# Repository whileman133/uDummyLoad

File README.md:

# 20W/50Ω μDummy RF Load with Wattmeter

This is the home of the design files and firmware for the μDummy RF Load project. See the description of the unit and the resources in this repo below.

## Description

This micro-size 50Ω RF dummy load with built-in wattmeter is well-suited for testing portable rigs. 
The glass LCD provides time-average power readings between 0.15 and 20W with 0.1W precision. 
Batteries are not required, as the unit draws power from the RF source, consuming a maximum of 3.0mA at the full rated input power. 
The board itself serves as a heatsink provided the operator limits the duration of the RF input. 
Improve the accuracy by loading a calibration table of up to 60 rows into EEPROM using an Arduino microcontroller.

## Organization of this Repo

- `2_Documentation/`: datasheet and documentation for the μDummy load unit
- `3_Mechanical/`: mechanical design files (primarily thermal analysis)
- `3_Electrical/`: KiCAD design files and LTspice simulation files
- `4_Software/`: firmware files
  - `uDummyLoad_PIC18F24Q10.X/`: firmware for the PIC microcontroller
  - `uDummyLoad_TranslatorArduino/`: Arduino sketch for uploading calibration table to the unit with an Arduino microcontroller

 ## License

Apache License, Version 2.0. See `LICENSE`.

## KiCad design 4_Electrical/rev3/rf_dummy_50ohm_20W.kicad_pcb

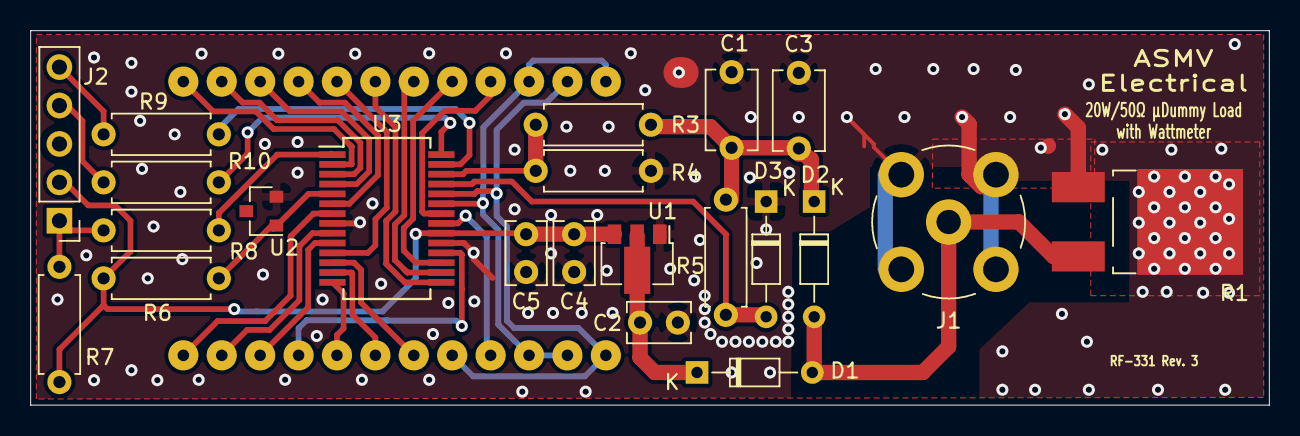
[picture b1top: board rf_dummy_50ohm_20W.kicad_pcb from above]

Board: 2 copper layers, 81.9 x 24.8 mm, 23 parts (1 on the bottom side), 33 nets.

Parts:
C1, C3: 5.6n; C_Disc_D5.1mm_W3.2mm_P5.00mm
C2: 1u 100V; C_Rect_L4.0mm_W2.5mm_P2.50mm
C4: 1u; C_Rect_L4.0mm_W2.5mm_P2.50mm
C5: 10n; C_Rect_L4.0mm_W2.5mm_P2.50mm
D1, D2, D3: BAT46; D_DO-34_SOD68_P7.62mm_Horizontal
J1: 50-Ohm BNC Male; BNC_TEConnectivity_1478204_Vertical
J2: Conn_01x05_Male; PinHeader_1x05_P2.54mm_Vertical
R1: 50 1% 45W; TO-252-2_TabPin1
R3: 100k 0.1%; R_Axial_DIN0207_L6.3mm_D2.5mm_P7.62mm_Horizontal
R4: 10k 0.1%; R_Axial_DIN0207_L6.3mm_D2.5mm_P7.62mm_Horizontal
R5, R7: 100k; R_Axial_DIN0207_L6.3mm_D2.5mm_P7.62mm_Horizontal
R6: 2.4k; R_Axial_DIN0207_L6.3mm_D2.5mm_P7.62mm_Horizontal
R8, R9, R10: 75; R_Axial_DIN0207_L6.3mm_D2.5mm_P7.62mm_Horizontal
U1: ZXTR2005Z; SOT-89-3
U2: LM4040AIM3-4.1; SOT-23
U3: PIC18F24Q10-xSP; SSOP-28_5.3x10.2mm_P0.65mm
U4: LCD-S301C31TF

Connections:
/ICSPCLK: J2.5, R9.1
/ICSPDAT: J2.4, R10.1
/LCD1_ADEG: U3.23, U4.2, U4.3, U4.22, U4.24
/LCD1_B: U3.22, U4.21
/LCD1_C: U3.21, U4.4
/LCD2_A: U3.15, U4.18
/LCD2_B: U3.11, U4.17
/LCD2_C: U3.14, U4.8
/LCD2_D: U3.13, U4.7
/LCD2_E: U3.12, U4.6
/LCD2_F: U3.16, U4.19
/LCD2_G: U3.17, U4.20
/LCD3_A: U3.3, U4.14
/LCD3_B: U3.2, U4.13
/LCD3_C: U3.7, U4.12
/LCD3_D: U3.9, U4.11
/LCD3_E: U3.10, U4.10
/LCD3_F: U3.4, U4.15
/LCD3_G: U3.6, U4.16
/LCD_COM: U3.24, U4.1, U4.5, U4.23
/LCD_DP2: U3.18, U4.9
/Vdiode: D3.2, R5.2, U3.25
/Vdivider: R3.1, R4.1, U3.26
/Vref+: R6.1, U2.1, U3.5
/~MCLR: J2.1, R7.2, R8.2
GND: C1.2, C2.2, C3.2, C4.2, C5.2, D3.1, J1.2, J2.3, R1.1, R4.2, U1.1, U2.2, U3.8, U3.19
unnamed: C1.1, C3.1, D2.1, R3.2, R5.1
unnamed: C2.1, D1.1, U1.2
unnamed: D1.2, D2.2, J1.1, R1.2
unnamed: R8.1, U3.1
unnamed: R9.2, U3.27
unnamed: R10.2, U3.28
VDD: C4.1, C5.1, J2.2, R6.2, R7.1, U1.3, U3.20

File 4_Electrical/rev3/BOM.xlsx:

Qty | Reference(s) | Value | Description | Man | Vendor | VendorPN | Quantity | Unit Price (1 assy) | Ext. Price (1 assy)
2 | C1, C3 | 5.6n | CAP CER 5600PF 100V C0G RADIAL |  | DigiKey | 445-181255-ND | 2 | 0.41 | 0.82
1 | C2, C4 | 1u 100V | CAP CER 1UF 100V X7R RADIAL | TDK Corporation | DigiKey | 445-173162-1-ND | 2 | 0.73 | 1.46
1 | C5 | 10n | CAP CER 10000PF 50V X7R RADIAL | TDK Corporation | DigiKey | 445-173264-1-ND | 1 | 0.28000000000000003 | 0.28000000000000003
3 | D1, D2, D3 | BAT46 | DIODE SCHOTTKY 100V 150MA DO35 | Vishay | DigiKey | BAT46CT-ND | 3 | 0.46 | 1.3800000000000001
1 | J1 | 50-Ohm BNC Male | CONN BNC JACK STR 50 OHM PCB | TE Connectivity AMP Connectors | DigiKey | A97581-ND | 1 | 2.35 | 2.35
1 | R1 | 50 1% 45W | RES 50 OHM 1% 45W TO252 | Ohmite | DigiKey | TKH45P50R0FECT-ND | 1 | 2.52 | 2.52
1 | R3 | 100k 0.1% | RES 100K OHM 1/4W .1% AXIAL | Stackpole Electronics | DigiKey | RNF14BTE100KCT-ND | 1 | 0.6 | 0.6
1 | R4 | 10k 0.1% | RES 10K OHM 1/4W .1% AXIAL | Stackpole Electronics | DigiKey | RNF14BTE10K0CT-ND | 1 | 0.6 | 0.6
2 | R5, R7 | 100k | RES 100K OHM 1/4W 1% AXIAL | Yageo | DigiKey | 100KXBK-ND | 2 | 0.1 | 0.2
1 | R6 | 2.4k | RES 2.4K OHM 1/4W 5% AXIAL | Yageo | DigiKey | 2.4KQBK-ND | 1 | 0.1 | 0.1
3 | R8, R9, R10 | 75 | RES 75 OHM 1/4W 5% AXIAL | Yageo | DigiKey | 75QBK-ND | 3 | 0.1 | 0.30000000000000004
1 | U1 | ZXTR2005Z | IC REG LINEAR 5V 38MA SOT89 | Diodes Incorporated | DigiKey | ZXTR2005Z-13DICT-ND | 1 | 0.56000000000000005 | 0.56000000000000005
1 | U2 | LM4040AIM3-4.1 | IC VREF SHUNT 0.1% SOT23-3 | Microchip Technology | DigiKey | LM4040AIM3-4.1/NOPBCT-ND | 1 | 1.89 | 1.89
1 | U3 | PIC18F24Q10-xSP | IC MCU 8BIT 16KB FLASH 28SSOP | Microchip Technology | DigiKey | PIC18F24Q10-I/SS-ND | 1 | 0.99 | 0.99
1 | U4 | LCD-S301C31TF | LCD MOD 3DIG 3 X 1 TRANSFLECTIVE | Lumex Opto/Components Inc. | DigiKey | 67-1799-ND | 1 | 2.57 | 2.57
 |  |  |  |  |  |  |  | 1 assy > | 16.619999999999997
 |  |  |  |  |  |  |  | 10 assy > | 13.42 | ea
 |  |  |  |  |  |  |  | 30 assy > | 12.36 | ea
 |  |  |  |  |  |  |  | 60 assy > | 11.4 | ea
 |  |  |  |  |  |  |  | 100 assy > | 9.84 | ea
 |  |  |  |  |  |  |  | 250 assy > | 9.01 | ea
 |  |  |  |  |  |  |  | 500 assy > | 7.74 | ea
 |  |  |  |  |  |  |  | 1000 assy > | 7.05 | ea
 |  |  |  |  |  |  |  | 2000 assy > | 7 | ea

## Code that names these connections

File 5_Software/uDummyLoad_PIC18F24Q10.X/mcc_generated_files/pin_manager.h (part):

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// get/set LCD3_B aliases
#define LCD3_B_TRIS                 TRISAbits.TRISA0
#define LCD3_B_LAT                  LATAbits.LATA0
#define LCD3_B_PORT                 PORTAbits.RA0
#define LCD3_B_WPU                  WPUAbits.WPUA0
#define LCD3_B_OD                   ODCONAbits.ODCA0
#define LCD3_B_ANS                  ANSELAbits.ANSELA0
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// get/set LCD3_A aliases
#define LCD3_A_TRIS                 TRISAbits.TRISA1
#define LCD3_A_LAT                  LATAbits.LATA1
#define LCD3_A_PORT                 PORTAbits.RA1
#define LCD3_A_WPU                  WPUAbits.WPUA1
#define LCD3_A_OD                   ODCONAbits.ODCA1
#define LCD3_A_ANS                  ANSELAbits.ANSELA1
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// get/set LCD3_F aliases
#define LCD3_F_TRIS                 TRISAbits.TRISA2
#define LCD3_F_LAT                  LATAbits.LATA2
#define LCD3_F_PORT                 PORTAbits.RA2
#define LCD3_F_WPU                  WPUAbits.WPUA2
#define LCD3_F_OD                   ODCONAbits.ODCA2
#define LCD3_F_ANS                  ANSELAbits.ANSELA2
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// get/set LCD3_G aliases
#define LCD3_G_TRIS                 TRISAbits.TRISA4
#define LCD3_G_LAT                  LATAbits.LATA4
#define LCD3_G_PORT                 PORTAbits.RA4
#define LCD3_G_WPU                  WPUAbits.WPUA4
#define LCD3_G_OD                   ODCONAbits.ODCA4
#define LCD3_G_ANS                  ANSELAbits.ANSELA4
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// get/set LCD3_C aliases
#define LCD3_C_TRIS                 TRISAbits.TRISA5
#define LCD3_C_LAT                  LATAbits.LATA5
#define LCD3_C_PORT                 PORTAbits.RA5
#define LCD3_C_WPU                  WPUAbits.WPUA5
#define LCD3_C_OD                   ODCONAbits.ODCA5
#define LCD3_C_ANS                  ANSELAbits.ANSELA5
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// get/set LCD3_E aliases
#define LCD3_E_TRIS                 TRISAbits.TRISA6
#define LCD3_E_LAT                  LATAbits.LATA6
#define LCD3_E_PORT                 PORTAbits.RA6
#define LCD3_E_WPU                  WPUAbits.WPUA6
#define LCD3_E_OD                   ODCONAbits.ODCA6
#define LCD3_E_ANS                  ANSELAbits.ANSELA6
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// get/set LCD3_D aliases
#define LCD3_D_TRIS                 TRISAbits.TRISA7
#define LCD3_D_LAT                  LATAbits.LATA7
#define LCD3_D_PORT                 PORTAbits.RA7
#define LCD3_D_WPU                  WPUAbits.WPUA7
#define LCD3_D_OD                   ODCONAbits.ODCA7
#define LCD3_D_ANS                  ANSELAbits.ANSELA7
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// get/set LCD1_C aliases
#define LCD1_C_TRIS                 TRISBbits.TRISB0
#define LCD1_C_LAT                  LATBbits.LATB0
#define LCD1_C_PORT                 PORTBbits.RB0
#define LCD1_C_WPU                  WPUBbits.WPUB0
#define LCD1_C_OD                   ODCONBbits.ODCB0
#define LCD1_C_ANS                  ANSELBbits.ANSELB0
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// get/set LCD1_B aliases
#define LCD1_B_TRIS                 TRISBbits.TRISB1
#define LCD1_B_LAT                  LATBbits.LATB1
#define LCD1_B_PORT                 PORTBbits.RB1
#define LCD1_B_WPU                  WPUBbits.WPUB1
#define LCD1_B_OD                   ODCONBbits.ODCB1
#define LCD1_B_ANS                  ANSELBbits.ANSELB1
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// get/set LCD1_ADEG aliases
#define LCD1_ADEG_TRIS                 TRISBbits.TRISB2
#define LCD1_ADEG_LAT                  LATBbits.LATB2
#define LCD1_ADEG_PORT                 PORTBbits.RB2
#define LCD1_ADEG_WPU                  WPUBbits.WPUB2
#define LCD1_ADEG_OD                   ODCONBbits.ODCB2
#define LCD1_ADEG_ANS                  ANSELBbits.ANSELB2
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// get/set LCD_COM aliases
#define LCD_COM_TRIS                 TRISBbits.TRISB3
#define LCD_COM_LAT                  LATBbits.LATB3
#define LCD_COM_PORT                 PORTBbits.RB3
#define LCD_COM_WPU                  WPUBbits.WPUB3
#define LCD_COM_OD                   ODCONBbits.ODCB3
#define LCD_COM_ANS                  ANSELBbits.ANSELB3
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// get/set VDIODE aliases
#define VDIODE_TRIS                 TRISBbits.TRISB4
#define VDIODE_LAT                  LATBbits.LATB4
#define VDIODE_PORT                 PORTBbits.RB4
#define VDIODE_WPU                  WPUBbits.WPUB4
#define VDIODE_OD                   ODCONBbits.ODCB4
#define VDIODE_ANS                  ANSELBbits.ANSELB4
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// get/set VDIVIDER aliases
#define VDIVIDER_TRIS                 TRISBbits.TRISB5
#define VDIVIDER_LAT                  LATBbits.LATB5
#define VDIVIDER_PORT                 PORTBbits.RB5
#define VDIVIDER_WPU                  WPUBbits.WPUB5
#define VDIVIDER_OD                   ODCONBbits.ODCB5
#define VDIVIDER_ANS                  ANSELBbits.ANSELB5
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// get/set LCD2_B aliases
#define LCD2_B_TRIS                 TRISCbits.TRISC0
#define LCD2_B_LAT                  LATCbits.LATC0
#define LCD2_B_PORT                 PORTCbits.RC0
#define LCD2_B_WPU                  WPUCbits.WPUC0
#define LCD2_B_OD                   ODCONCbits.ODCC0
#define LCD2_B_ANS                  ANSELCbits.ANSELC0
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// get/set LCD2_E aliases
#define LCD2_E_TRIS                 TRISCbits.TRISC1
#define LCD2_E_LAT                  LATCbits.LATC1
#define LCD2_E_PORT                 PORTCbits.RC1
#define LCD2_E_WPU                  WPUCbits.WPUC1
#define LCD2_E_OD                   ODCONCbits.ODCC1
#define LCD2_E_ANS                  ANSELCbits.ANSELC1
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// get/set LCD2_D aliases
#define LCD2_D_TRIS                 TRISCbits.TRISC2
#define LCD2_D_LAT                  LATCbits.LATC2
#define LCD2_D_PORT                 PORTCbits.RC2
#define LCD2_D_WPU                  WPUCbits.WPUC2
#define LCD2_D_OD                   ODCONCbits.ODCC2
#define LCD2_D_ANS                  ANSELCbits.ANSELC2
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// get/set LCD2_C aliases
#define LCD2_C_TRIS                 TRISCbits.TRISC3
#define LCD2_C_LAT                  LATCbits.LATC3
#define LCD2_C_PORT                 PORTCbits.RC3
#define LCD2_C_WPU                  WPUCbits.WPUC3
#define LCD2_C_OD                   ODCONCbits.ODCC3
#define LCD2_C_ANS                  ANSELCbits.ANSELC3
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// get/set LCD2_A aliases
#define LCD2_A_TRIS                 TRISCbits.TRISC4
#define LCD2_A_LAT                  LATCbits.LATC4
#define LCD2_A_PORT                 PORTCbits.RC4
#define LCD2_A_WPU                  WPUCbits.WPUC4
#define LCD2_A_OD                   ODCONCbits.ODCC4
#define LCD2_A_ANS                  ANSELCbits.ANSELC4
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// get/set LCD2_F aliases
#define LCD2_F_TRIS                 TRISCbits.TRISC5
#define LCD2_F_LAT                  LATCbits.LATC5
#define LCD2_F_PORT                 PORTCbits.RC5
#define LCD2_F_WPU                  WPUCbits.WPUC5
#define LCD2_F_OD                   ODCONCbits.ODCC5
#define LCD2_F_ANS                  ANSELCbits.ANSELC5
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// get/set LCD2_G aliases
#define LCD2_G_TRIS                 TRISCbits.TRISC6
#define LCD2_G_LAT                  LATCbits.LATC6
#define LCD2_G_PORT                 PORTCbits.RC6
#define LCD2_G_WPU                  WPUCbits.WPUC6
#define LCD2_G_OD                   ODCONCbits.ODCC6
#define LCD2_G_ANS                  ANSELCbits.ANSELC6
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// get/set LCD_DP2 aliases
#define LCD_DP2_TRIS                 TRISCbits.TRISC7
#define LCD_DP2_LAT                  LATCbits.LATC7
#define LCD_DP2_PORT                 PORTCbits.RC7
#define LCD_DP2_WPU                  WPUCbits.WPUC7
#define LCD_DP2_OD                   ODCONCbits.ODCC7
#define LCD_DP2_ANS                  ANSELCbits.ANSELC7
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
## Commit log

2024-02-06 Create LICENSE
2024-02-06 Update LICENSE

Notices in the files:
5_Software/uDummyLoad_PIC18F24Q10.X/mcc_generated_files/pin_manager.h:
(c) 2018 Microchip Technology Inc. and its subsidiaries.
